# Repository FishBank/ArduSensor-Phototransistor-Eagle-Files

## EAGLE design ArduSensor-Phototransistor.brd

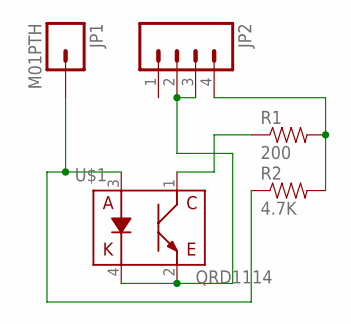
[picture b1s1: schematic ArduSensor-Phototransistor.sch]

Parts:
JP1: M01PTH; 1X01
JP2: M04PTH; 1X04
R1: 200; AXIAL-0.3
R2: 4.7K; AXIAL-0.3
U$1: QRD1114

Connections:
unnamed: JP1.1, R2.P$1 (1), U$1.3 (A)
unnamed: R1.P$1 (1), U$1.1 (E)
unnamed: JP2.2, JP2.3, U$1.2 (C), U$1.4 (K)
unnamed: JP2.4, R1.P$2 (2), R2.P$2 (2)

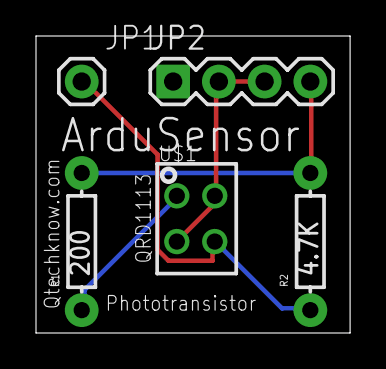
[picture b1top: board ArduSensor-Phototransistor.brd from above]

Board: 2 copper layers, 17.4 x 16.5 mm, 5 parts (0 on the bottom side), 4 nets.

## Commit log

2012-07-13 Schematic

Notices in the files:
parts and their libraries:
SFE Connectors: Licensing: CC v3.0 Share-Alike You are welcome to use this library for commercial purposes.
